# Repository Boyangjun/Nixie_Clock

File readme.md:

First of all, what is a nixie clock?

They are essentially timekeeping clocks, but nixie clock uses **nixie tube** to show the time. Nixie tube is a kind of ion tube that uses the principle of gas nixie discharge to work, the color of nixie determines by the composition of gas filled in the tube, such as neon to red,  argon to light purple, mercury to light blue, helium to pink and so on.

Nixie tube has some characteristics, such as power supply of 170V (so you need to do special boost), it’s life span is about one or two years, and keeping the number to tubes for a long time may lead to the cathode of tube poisoning(harmless for humans), so if you want to display the time, you need to do some small actions to change the numbers.

Light nixie is comfortable to look at, it will be a cool clock if together with RGB, Wi-Fi, temperature and humidity sensors, it should be a cool clock.

## Component Selection

* **Nixie Tube** I chose the IN-14 from the former Soviet Union, a new one costs 100 yuan, and a second-hand costs 50 yuan. In addition to the 0-9 numbers, there are left and right decimal points to show. It has a nice color and high quality.
* **Main control chip**I chose Arduino atmega 328p , because it can be developed directly on Arduino IDE, which is convenient for Mac computers, and there are extension libraries that can simplify programming(although it’s not a good thing for learning)
* **Time Receive** I chose esp8266 12F to obtain global standard time via ump connection of NTP Server
* **Boost**I just buy others boost module which can boost 5V to 170V, I recommend to design by yourself but I don’t have time.
* **RGB**I chose ws2812, which is a common one, it show fast and accurate and can be develop easily by Arduino IDE.
* PS: I didn’t use **Time Chip** like DS1302, Its really a failure, if the connection to NTP Server is not good, time shows in a bad way like jumping a few seconds, and if no Wi-Fi, it is unable to obtain time. To solve this problem, I added  DS3231 time count module, so it only need to get time when switching on, even if the power cut off, the time can be continued by button battery power.

## Circuit Design

* Nixie Clock Driver: 74HC595 + A42triode, easy to design and saving IO ports.

## Program Design

Program consist of two parts: setup() and loop(), the former only run once after power on, while loop() runs once and once until power off. So setup() contains some initialize likeWi-Fi connection, NTP Server connection, RGB, etc. While Loop() keeps receiving time  every second (or faster) and some other functions.

Some great libraries here, Thanks to their author!

Wifi and NTP Server：https://github.com/bportaluri/WiFiEsp

75HC595 Driver：[GitHub - Simsso/ShiftRegister74HC595: Arduino library that simplifies the usage of shift registers](https://github.com/Simsso/ShiftRegister74HC595)

RGB Driver：https://github.com/adafruit/Adafruit_NeoPixel

## Finally
I really hope this will help you for designing nixie clock. Any questions or suggestions, e-mail me! (boyangjun@bupt.edu.cn)

[image:BA12CFBF-97E2-4782-B7CB-3B10783BA695-6988-0000322A6EA5FA8B/IMG_20190530_185942.jpg]

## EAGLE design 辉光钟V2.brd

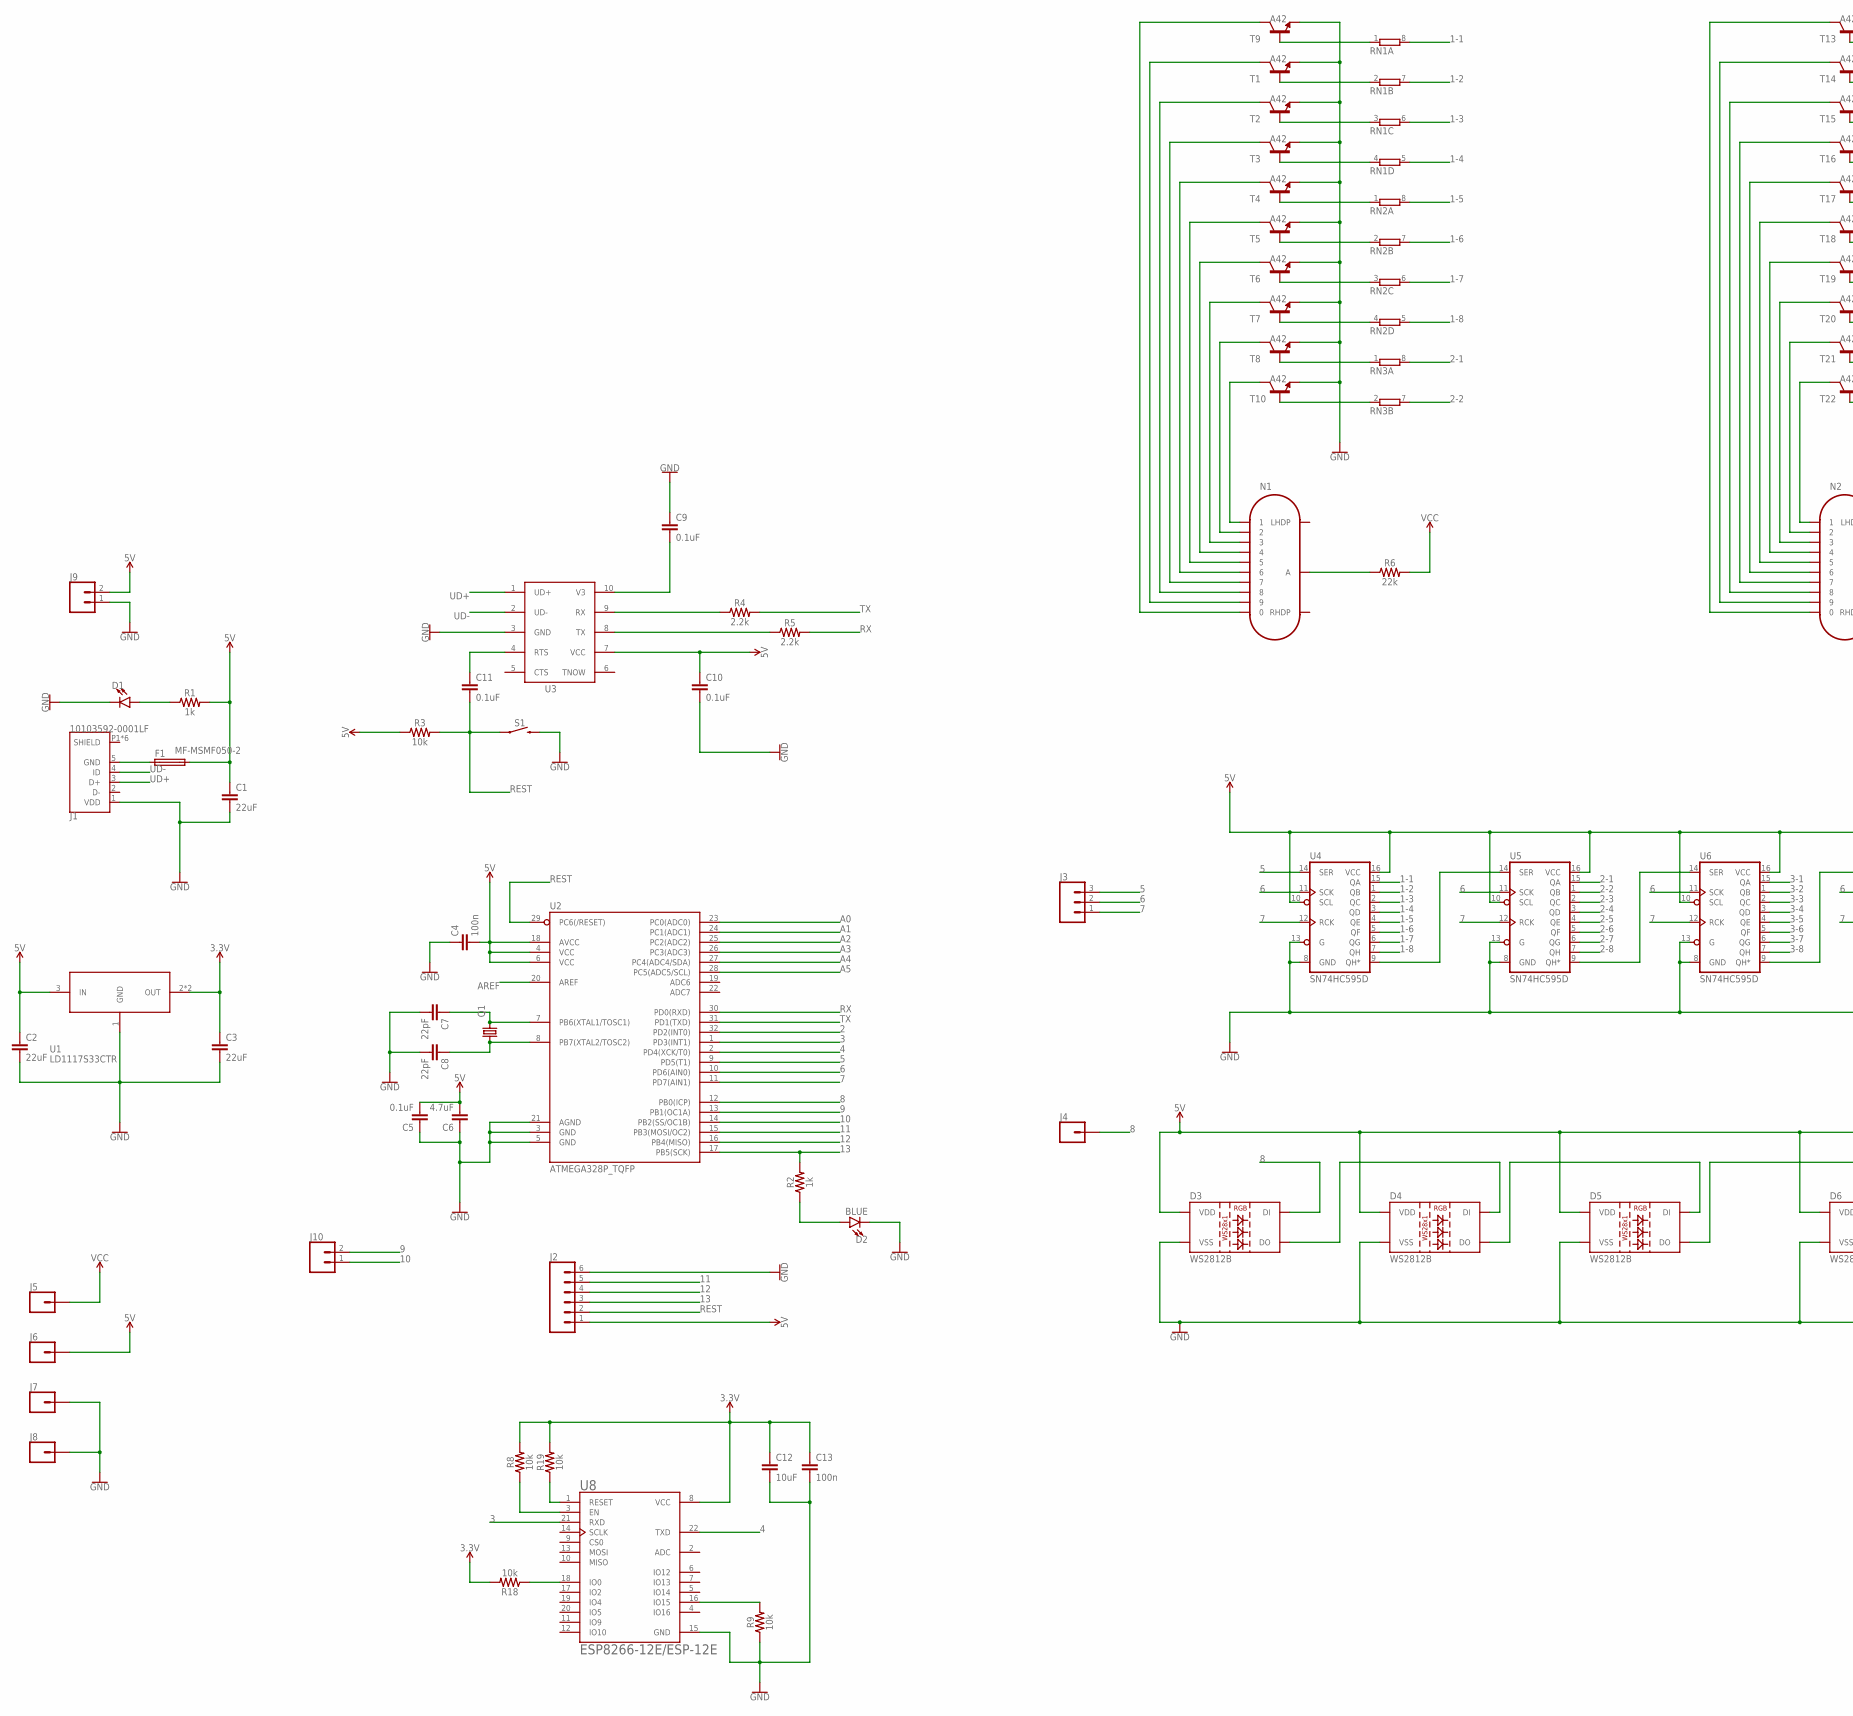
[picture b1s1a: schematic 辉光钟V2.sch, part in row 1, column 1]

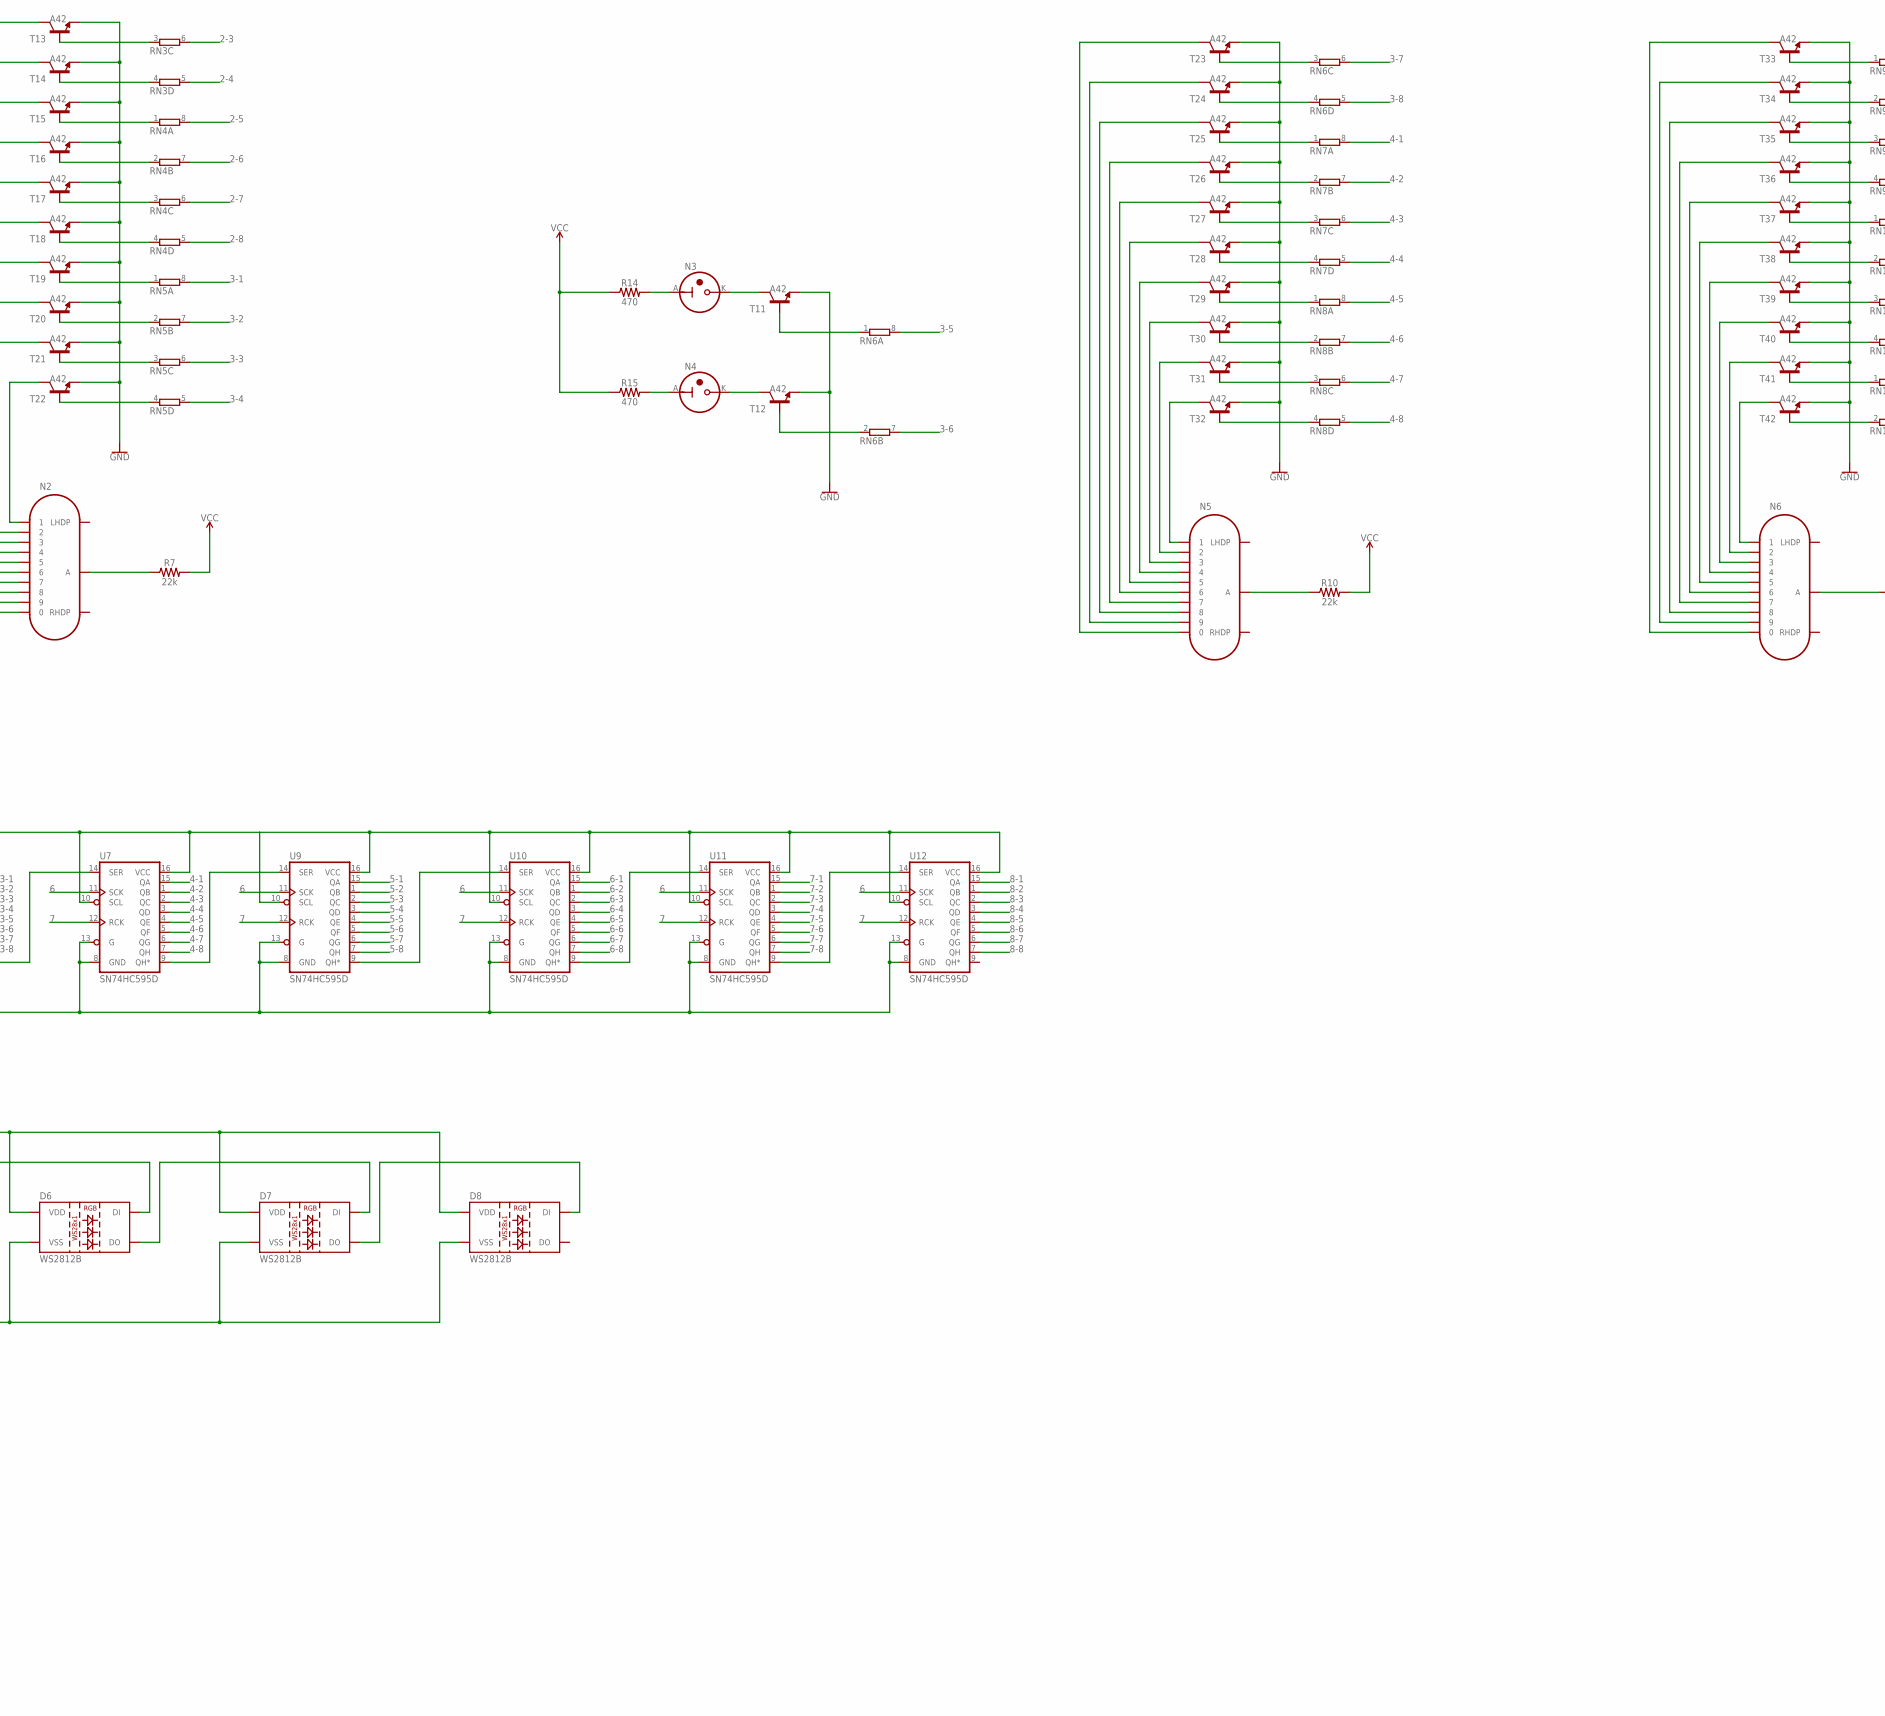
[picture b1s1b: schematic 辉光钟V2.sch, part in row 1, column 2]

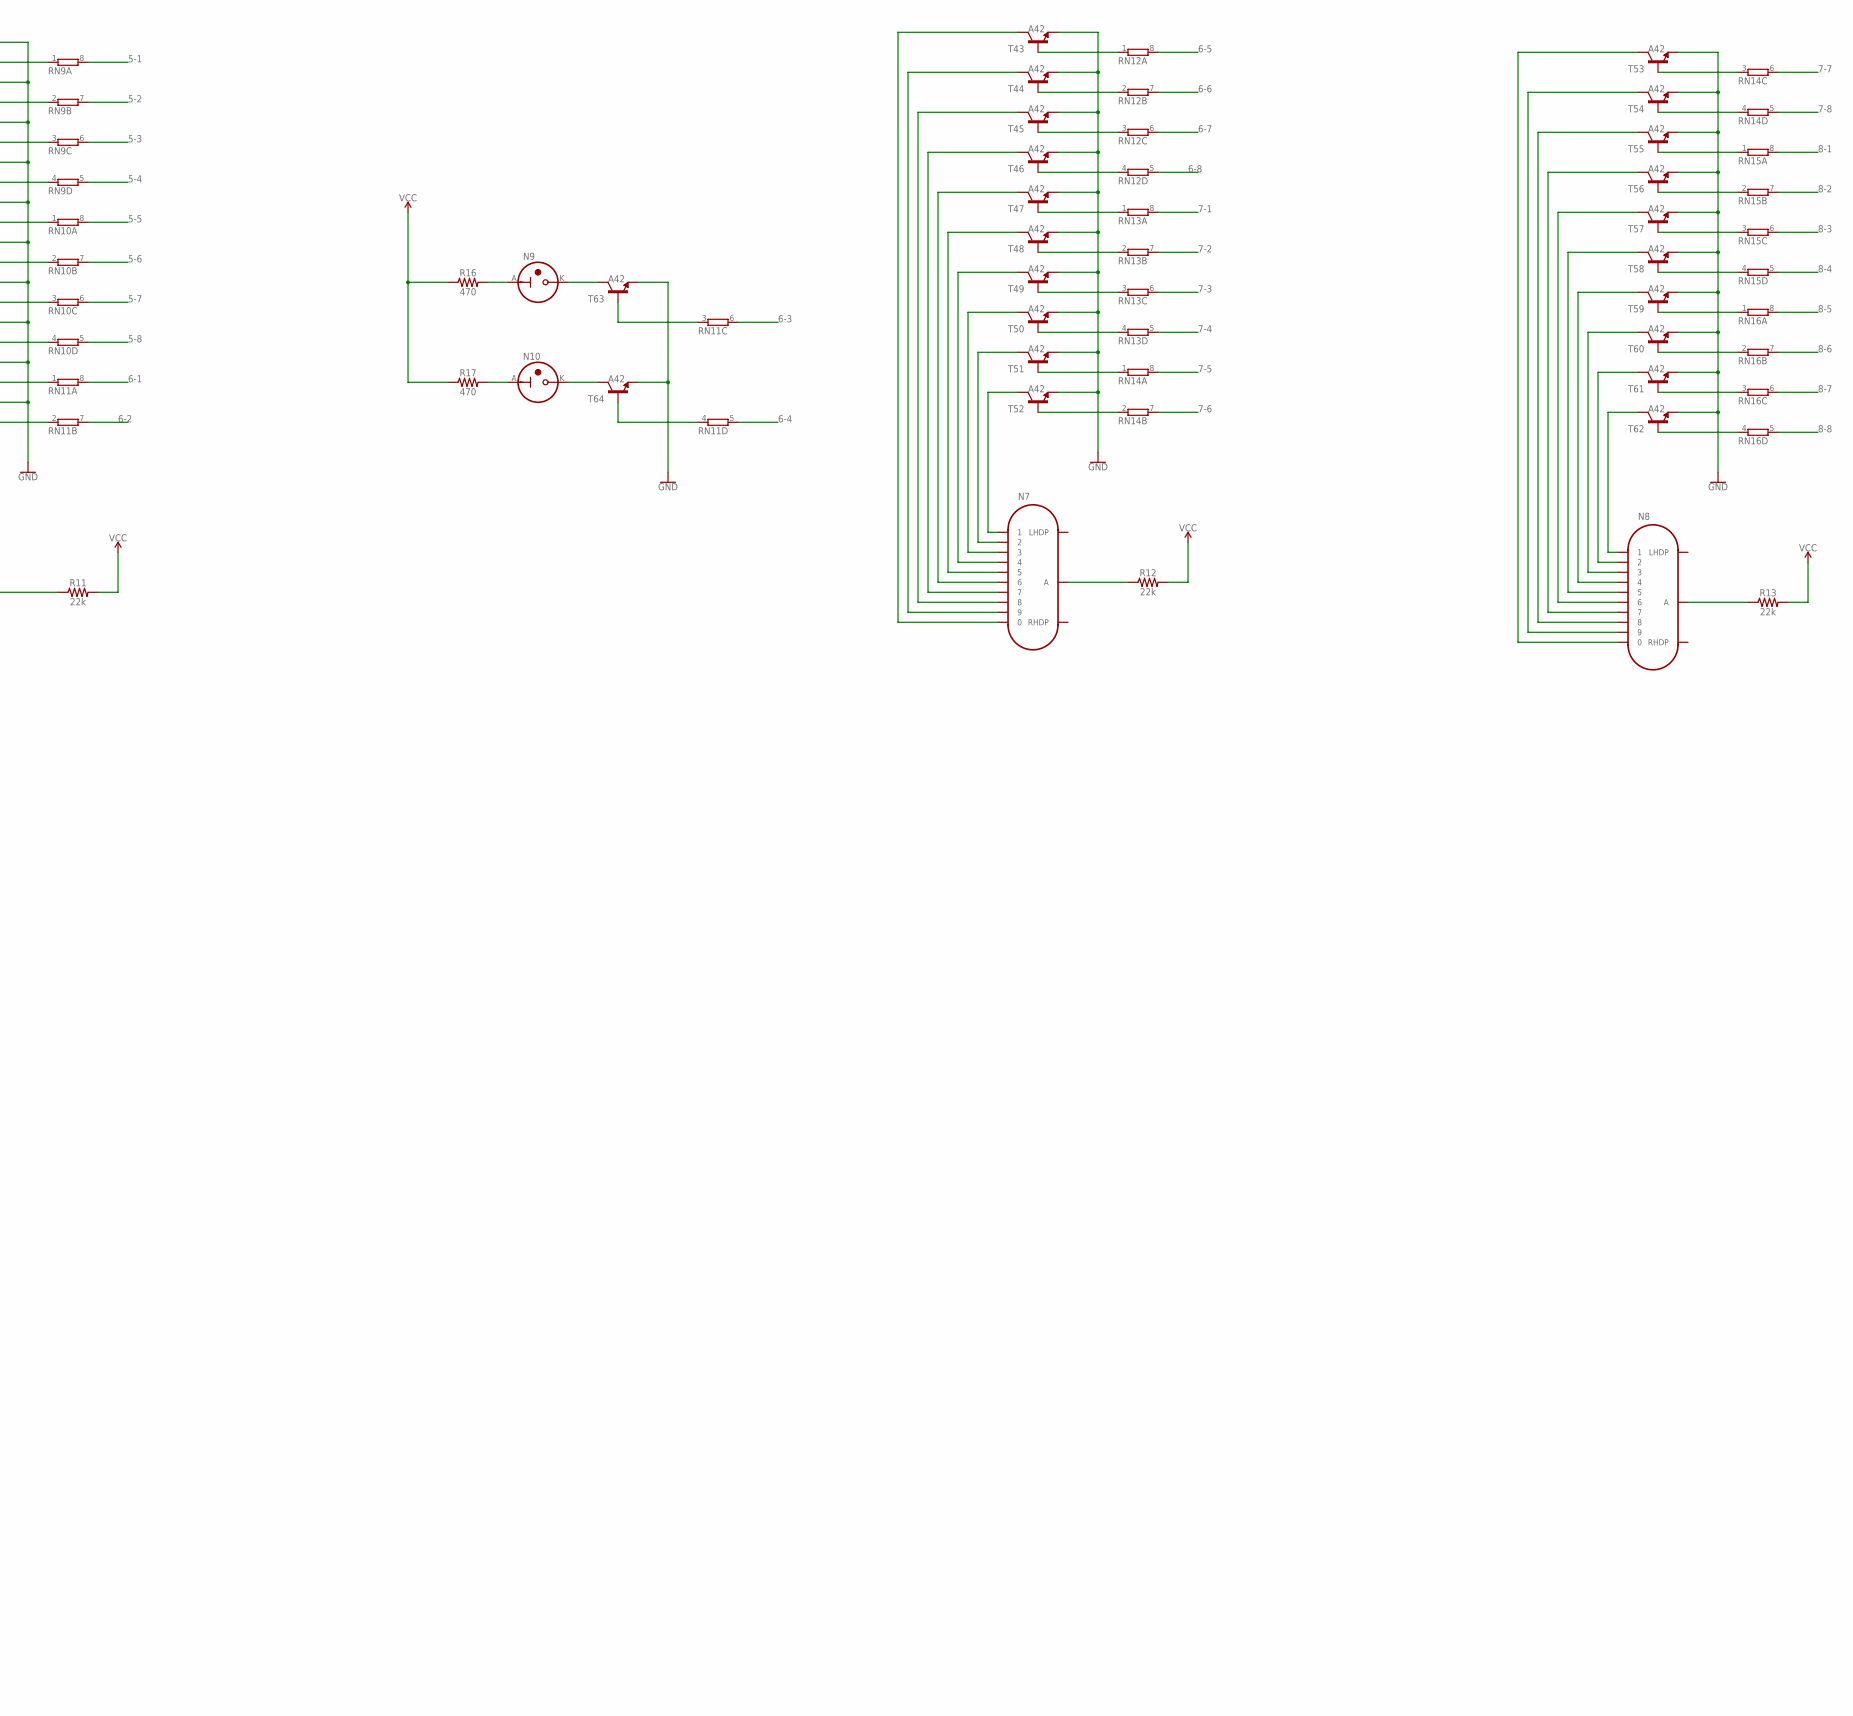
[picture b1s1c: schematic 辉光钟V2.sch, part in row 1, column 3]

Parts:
C1, C2, C3: 22uF; 0805
C4, C13: 100n; 0603
C5, C9, C10, C11: 0.1uF; 0603
C6: 4.7uF; 0603
C7, C8: 22pF; 0603
C12: 10uF; 0603
D1: LED0603; LED-0603
D2: BLUE; LED-0603
D3, D4, D5, D6, D7, D8: WS2812B
F1: MF-MSMF050-2; FUSM1812X02
J1: 10103592-0001LF; AMPHENOL_10103592-0001LF
J2: CONN_06NO_SILK_FEMALE_PTH; 1X06_NO_SILK
J3: CONN_03; 1X03
J4, J5, J6, J7, J8: CONN_01; 1X01
J9, J10: CONN_02; 1X02
N1, N2, N5, N6, N7, N8: IN-14
N3, N4, N9, N10: IN-3
Q1: KX-7; 3.2X2.5_KX-7
R1, R2: 1k; 0603
R3, R8, R9, R18, R19: 10k; 0603
R4, R5: 2.2k; 0603
R6, R7, R10, R11, R12, R13: 22k; 0603
R14, R15, R16, R17: 470; 0603
RN1, RN2, RN3, RN4, RN5, RN6, RN7, RN8, RN9, RN10, RN11, RN12, RN13, RN14, RN15, RN16: 4R-N0603-ARC; 0603-ARC
S1: MOMENTARY-SWITCH-SPST-SMD-6.0X3.5MM; TACTILE_SWITCH_SMD_6.0X3.5MM
T1, T2, T3, T4, T5, T6, T7, T8, T9, T10, T11, T12, T13, T14, T15, T16, T17, T18, T19, T20, T21, T22, T23, T24, T25, T26, T27, T28, T29, T30, T31, T32, T33, T34, T35, T36, T37, T38, T39, T40, T41, T42, T43, T44, T45, T46, T47, T48, T49, T50, T51, T52, T53, T54, T55, T56, T57, T58, T59, T60, T61, T62, T63, T64: A42; SOT23
U1: LD1117S33CTR; SOT223
U2: ATMEGA328P_TQFP; TQFP32-08
U3: CH340ESMD; MSOP10
U4, U5, U6, U7, U9, U10, U11, U12: SN74HC595D; SO16
U8: ESP8266-12E/ESP-12E; XCVR_ESP8266-12E/ESP-12E

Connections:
1-1: RN1.8 (2), U4.15 (QA)
1-2: RN1.7 (2), U4.1 (QB)
1-3: RN1.6 (2), U4.2 (QC)
1-4: RN1.5 (2), U4.3 (QD)
1-5: RN2.8 (2), U4.4 (QE)
1-6: RN2.7 (2), U4.5 (QF)
1-7: RN2.6 (2), U4.6 (QG)
1-8: RN2.5 (2), U4.7 (QH)
2: U2.32 (PD2(INT0))
2-1: RN3.8 (2), U5.15 (QA)
2-2: RN3.7 (2), U5.1 (QB)
2-3: RN3.6 (2), U5.2 (QC)
2-4: RN3.5 (2), U5.3 (QD)
2-5: RN4.8 (2), U5.4 (QE)
2-6: RN4.7 (2), U5.5 (QF)
2-7: RN4.6 (2), U5.6 (QG)
2-8: RN4.5 (2), U5.7 (QH)
3: U2.1 (PD3(INT1)), U8.21 (RXD)
3-1: RN5.8 (2), U6.15 (QA)
3-2: RN5.7 (2), U6.1 (QB)
3-3: RN5.6 (2), U6.2 (QC)
3-4: RN5.5 (2), U6.3 (QD)
3-5: RN6.8 (2), U6.4 (QE)
3-6: RN6.7 (2), U6.5 (QF)
3-7: RN6.6 (2), U6.6 (QG)
3-8: RN6.5 (2), U6.7 (QH)
3.3V: C3.1, C12.1, C13.1, R8.2, R18.2, R19.2, U1.2 (OUT), U1.4 (OUT), U8.8 (VCC)
4: U2.2 (PD4(XCK/T0)), U8.22 (TXD)
4-1: RN7.8 (2), U7.15 (QA)
4-2: RN7.7 (2), U7.1 (QB)
4-3: RN7.6 (2), U7.2 (QC)
4-4: RN7.5 (2), U7.3 (QD)
4-5: RN8.8 (2), U7.4 (QE)
4-6: RN8.7 (2), U7.5 (QF)
4-7: RN8.6 (2), U7.6 (QG)
4-8: RN8.5 (2), U7.7 (QH)
5: J3.3, U2.9 (PD5(T1)), U4.14 (SER)
5-1: RN9.8 (2), U9.15 (QA)
5-2: RN9.7 (2), U9.1 (QB)
5-3: RN9.6 (2), U9.2 (QC)
5-4: RN9.5 (2), U9.3 (QD)
5-5: RN10.8 (2), U9.4 (QE)
5-6: RN10.7 (2), U9.5 (QF)
5-7: RN10.6 (2), U9.6 (QG)
5-8: RN10.5 (2), U9.7 (QH)
5V: C1.1, C2.1, C4.2, C5.2, C6.2, C10.1, D3.1 (VDD), D4.1 (VDD), D5.1 (VDD), D6.1 (VDD), D7.1 (VDD), D8.1 (VDD), F1.2, J2.1, J6.1, J9.2, R1.2, R3.1, U1.3 (IN), U2.4 (VCC), U2.6 (VCC), U2.18 (AVCC), U3.7 (VCC), U4.10 (SCL), U4.16 (VCC), U5.10 (SCL), U5.16 (VCC), U6.10 (SCL), U6.16 (VCC), U7.10 (SCL), U7.16 (VCC), U9.10 (SCL), U9.16 (VCC), U10.10 (SCL), U10.16 (VCC), U11.10 (SCL), U11.16 (VCC), U12.10 (SCL), U12.16 (VCC)
6: J3.2, U2.10 (PD6(AIN0)), U4.11 (SCK), U5.11 (SCK), U6.11 (SCK), U7.11 (SCK), U9.11 (SCK), U10.11 (SCK), U11.11 (SCK), U12.11 (SCK)
6-1: RN11.8 (2), U10.15 (QA)
6-2: RN11.7 (2), U10.1 (QB)
6-3: RN11.6 (2), U10.2 (QC)
6-4: RN11.5 (2), U10.3 (QD)
6-5: RN12.8 (2), U10.4 (QE)
6-6: RN12.7 (2), U10.5 (QF)
6-7: RN12.6 (2), U10.6 (QG)
6-8: RN12.5 (2), U10.7 (QH)
7: J3.1, U2.11 (PD7(AIN1)), U4.12 (RCK), U5.12 (RCK), U6.12 (RCK), U7.12 (RCK), U9.12 (RCK), U10.12 (RCK), U11.12 (RCK), U12.12 (RCK)
7-1: RN13.8 (2), U11.15 (QA)
7-2: RN13.7 (2), U11.1 (QB)
7-3: RN13.6 (2), U11.2 (QC)
7-4: RN13.5 (2), U11.3 (QD)
7-5: RN14.8 (2), U11.4 (QE)
7-6: RN14.7 (2), U11.5 (QF)
7-7: RN14.6 (2), U11.6 (QG)
7-8: RN14.5 (2), U11.7 (QH)
8: D3.4 (DI), J4.1, U2.12 (PB0(ICP))
8-1: RN15.8 (2), U12.15 (QA)
8-2: RN15.7 (2), U12.1 (QB)
8-3: RN15.6 (2), U12.2 (QC)
8-4: RN15.5 (2), U12.3 (QD)
8-5: RN16.8 (2), U12.4 (QE)
8-6: RN16.7 (2), U12.5 (QF)
8-7: RN16.6 (2), U12.6 (QG)
8-8: RN16.5 (2), U12.7 (QH)
9: J10.2, U2.13 (PB1(OC1A))
10: J10.1, U2.14 (PB2(SS/OC1B))
11: J2.5, U2.15 (PB3(MOSI/OC2))
12: J2.4, U2.16 (PB4(MISO))
13: J2.3, R2.2, U2.17 (PB5(SCK))
A0: U2.23 (PC0(ADC0))
A1: U2.24 (PC1(ADC1))
A2: U2.25 (PC2(ADC2))
A3: U2.26 (PC3(ADC3))
A4: U2.27 (PC4(ADC4/SDA))
A5: U2.28 (PC5(ADC5/SCL))
AREF: U2.20 (AREF)
GND: C1.2, C2.2, C3.2, C4.1, C5.1, C6.1, C7.2, C8.2, C9.1, C10.2, C12.2, C13.2, D1.C, D2.C, D3.3 (VSS), D4.3 (VSS), D5.3 (VSS), D6.3 (VSS), D7.3 (VSS), D8.3 (VSS), J1.1 (VDD), J2.6, J7.1, J8.1, J9.1, R9.1, S1.2, T1.2 (E), T2.2 (E), T3.2 (E), T4.2 (E), T5.2 (E), T6.2 (E), T7.2 (E), T8.2 (E), T9.2 (E), T10.2 (E), T11.2 (E), T12.2 (E), T13.2 (E), T14.2 (E), T15.2 (E), T16.2 (E), T17.2 (E), T18.2 (E), T19.2 (E), T20.2 (E), T21.2 (E), T22.2 (E), T23.2 (E), T24.2 (E), T25.2 (E), T26.2 (E), T27.2 (E), T28.2 (E), T29.2 (E), T30.2 (E), T31.2 (E), T32.2 (E), T33.2 (E), T34.2 (E), T35.2 (E), T36.2 (E), T37.2 (E), T38.2 (E), T39.2 (E), T40.2 (E), T41.2 (E), T42.2 (E), T43.2 (E), T44.2 (E), T45.2 (E), T46.2 (E), T47.2 (E), T48.2 (E), T49.2 (E), T50.2 (E), T51.2 (E), T52.2 (E), T53.2 (E), T54.2 (E), T55.2 (E), T56.2 (E), T57.2 (E), T58.2 (E), T59.2 (E), T60.2 (E), T61.2 (E), T62.2 (E), T63.2 (E), T64.2 (E), U1.1 (GND), U2.3 (GND), U2.5 (GND), U2.21 (AGND), U3.3 (GND), U4.8 (GND), U4.13 (G), U5.8 (GND), U5.13 (G), U6.8 (GND), U6.13 (G), U7.8 (GND), U7.13 (G), U8.15 (GND), U9.8 (GND), U9.13 (G), U10.8 (GND), U10.13 (G), U11.8 (GND), U11.13 (G), U12.8 (GND), U12.13 (G)
unnamed: F1.1, J1.5 (GND)
unnamed: U4.9 (QH*), U5.14 (SER)
unnamed: U5.9 (QH*), U6.14 (SER)
unnamed: C7.1, Q1.3 (2), U2.7 (PB6(XTAL1/TOSC1))
unnamed: D1.A, R1.1
unnamed: C8.1, Q1.1, U2.8 (PB7(XTAL2/TOSC2))
unnamed: U6.9 (QH*), U7.14 (SER)
unnamed: D2.A, R2.1
unnamed: C11.1, U3.4 (RTS)
unnamed: N1.1, T10.3 (C)
unnamed: N1.2, T8.3 (C)
unnamed: N1.3, T7.3 (C)
unnamed: N1.4, T6.3 (C)
unnamed: N1.5, T5.3 (C)
unnamed: N1.6, T4.3 (C)
unnamed: N1.7, T3.3 (C)
unnamed: N1.8, T2.3 (C)
unnamed: N1.9, T1.3 (C)
unnamed: N1.0, T9.3 (C)
unnamed: RN1.1, T9.1 (B)
unnamed: RN1.2 (1), T1.1 (B)
unnamed: RN1.3 (1), T2.1 (B)
unnamed: RN1.4 (1), T3.1 (B)
unnamed: R4.1, U3.9 (RX)
unnamed: R5.1, U3.8 (TX)
unnamed: RN2.1, T4.1 (B)
unnamed: RN2.2 (1), T5.1 (B)
unnamed: C9.2, U3.10 (V3)
unnamed: RN2.3 (1), T6.1 (B)
unnamed: RN2.4 (1), T7.1 (B)
unnamed: N1.A, R6.1
unnamed: RN3.1, T8.1 (B)
unnamed: RN3.2 (1), T10.1 (B)
unnamed: N2.1, T22.3 (C)
unnamed: N2.2, T21.3 (C)
unnamed: N2.3, T20.3 (C)
unnamed: N2.4, T19.3 (C)
unnamed: N2.5, T18.3 (C)
unnamed: N2.6, T17.3 (C)
unnamed: N2.7, T16.3 (C)
unnamed: N2.8, T15.3 (C)
unnamed: N2.9, T14.3 (C)
unnamed: N2.0, T13.3 (C)
unnamed: N2.A, R7.1
unnamed: RN3.3 (1), T13.1 (B)
unnamed: RN3.4 (1), T14.1 (B)
unnamed: RN4.1, T15.1 (B)
unnamed: RN4.2 (1), T16.1 (B)
unnamed: RN4.3 (1), T17.1 (B)
unnamed: RN4.4 (1), T18.1 (B)
unnamed: RN5.1, T19.1 (B)
unnamed: RN5.2 (1), T20.1 (B)
unnamed: RN5.3 (1), T21.1 (B)
unnamed: RN5.4 (1), T22.1 (B)
unnamed: R8.1, U8.3 (EN)
unnamed: R9.2, U8.16 (IO15)
unnamed: U7.9 (QH*), U9.14 (SER)
unnamed: N5.1, T32.3 (C)
unnamed: N5.2, T31.3 (C)
unnamed: N5.3, T30.3 (C)
unnamed: N5.4, T29.3 (C)
unnamed: N5.5, T28.3 (C)
unnamed: N5.6, T27.3 (C)
unnamed: N5.7, T26.3 (C)
unnamed: N5.8, T25.3 (C)
unnamed: N5.9, T24.3 (C)
unnamed: N5.0, T23.3 (C)
unnamed: N5.A, R10.1
unnamed: RN6.3 (1), T23.1 (B)
unnamed: RN6.4 (1), T24.1 (B)
unnamed: RN7.1, T25.1 (B)
unnamed: RN7.2 (1), T26.1 (B)
unnamed: RN7.3 (1), T27.1 (B)
unnamed: RN7.4 (1), T28.1 (B)
unnamed: RN8.1, T29.1 (B)
unnamed: RN8.2 (1), T30.1 (B)
unnamed: RN8.3 (1), T31.1 (B)
unnamed: RN8.4 (1), T32.1 (B)
unnamed: N6.1, T42.3 (C)
unnamed: N6.2, T41.3 (C)
unnamed: N6.3, T40.3 (C)
unnamed: N6.4, T39.3 (C)
unnamed: N6.5, T38.3 (C)
unnamed: N6.6, T37.3 (C)
unnamed: N6.7, T36.3 (C)
unnamed: N6.8, T35.3 (C)
unnamed: N6.9, T34.3 (C)
unnamed: N6.0, T33.3 (C)
unnamed: N6.A, R11.1
unnamed: RN9.1, T33.1 (B)
unnamed: RN9.2 (1), T34.1 (B)
unnamed: RN9.3 (1), T35.1 (B)
unnamed: RN9.4 (1), T36.1 (B)
unnamed: RN10.1, T37.1 (B)
unnamed: RN10.2 (1), T38.1 (B)
unnamed: RN10.3 (1), T39.1 (B)
unnamed: RN10.4 (1), T40.1 (B)
unnamed: RN11.1, T41.1 (B)
unnamed: RN11.2 (1), T42.1 (B)
unnamed: N7.1, T52.3 (C)
unnamed: N7.2, T51.3 (C)
unnamed: N7.3, T50.3 (C)
unnamed: N7.4, T49.3 (C)
unnamed: N7.5, T48.3 (C)
unnamed: N7.6, T47.3 (C)
unnamed: N7.7, T46.3 (C)
unnamed: N7.8, T45.3 (C)
unnamed: N7.9, T44.3 (C)
unnamed: N7.0, T43.3 (C)
unnamed: N7.A, R12.1
unnamed: RN12.1, T43.1 (B)
unnamed: RN12.2 (1), T44.1 (B)
unnamed: RN12.3 (1), T45.1 (B)
unnamed: RN12.4 (1), T46.1 (B)
unnamed: RN13.1, T47.1 (B)
unnamed: RN13.2 (1), T48.1 (B)
unnamed: RN13.3 (1), T49.1 (B)
unnamed: RN13.4 (1), T50.1 (B)
unnamed: RN14.1, T51.1 (B)
unnamed: RN14.2 (1), T52.1 (B)
unnamed: N8.1, T62.3 (C)
unnamed: N8.2, T61.3 (C)
unnamed: N8.3, T60.3 (C)
unnamed: N8.4, T59.3 (C)
unnamed: N8.5, T58.3 (C)
unnamed: N8.6, T57.3 (C)
unnamed: N8.7, T56.3 (C)
unnamed: N8.8, T55.3 (C)
unnamed: N8.9, T54.3 (C)
unnamed: N8.0, T53.3 (C)
unnamed: N8.A, R13.1
unnamed: RN14.3 (1), T53.1 (B)
unnamed: RN14.4 (1), T54.1 (B)
unnamed: RN15.1, T55.1 (B)
unnamed: RN15.2 (1), T56.1 (B)
unnamed: RN15.3 (1), T57.1 (B)
unnamed: RN15.4 (1), T58.1 (B)
unnamed: RN16.1, T59.1 (B)
unnamed: RN16.2 (1), T60.1 (B)
unnamed: RN16.3 (1), T61.1 (B)
unnamed: RN16.4 (1), T62.1 (B)
unnamed: N3.A, R14.2
unnamed: N3.K, T11.3 (C)
unnamed: N4.A, R15.2
unnamed: N4.K, T12.3 (C)
unnamed: RN6.1, T11.1 (B)
unnamed: RN6.2 (1), T12.1 (B)
unnamed: N9.A, R16.2
unnamed: N9.K, T63.3 (C)
unnamed: N10.A, R17.2
unnamed: N10.K, T64.3 (C)
unnamed: RN11.3 (1), T63.1 (B)
unnamed: RN11.4 (1), T64.1 (B)
unnamed: R19.1, U8.1 (RESET)
unnamed: D3.2 (DO), D4.4 (DI)
unnamed: R18.1, U8.18 (IO0)
unnamed: D4.2 (DO), D5.4 (DI)
unnamed: D5.2 (DO), D6.4 (DI)
unnamed: D6.2 (DO), D7.4 (DI)
unnamed: D7.2 (DO), D8.4 (DI)
unnamed: U10.9 (QH*), U11.14 (SER)
unnamed: U11.9 (QH*), U12.14 (SER)
unnamed: U9.9 (QH*), U10.14 (SER)
REST: C11.2, J2.2, R3.2, S1.1, U2.29 (PC6(/RESET))
RX: R5.2, U2.30 (PD0(RXD))
SHIELD: J1.P1 (SHIELD), J1.P2 (SHIELD), J1.P3 (SHIELD), J1.P4 (SHIELD), J1.P5 (SHIELD), J1.P6 (SHIELD)
TX: R4.2, U2.31 (PD1(TXD))
UD+: J1.3 (D+), U3.1 (UD+)
UD-: J1.4 (ID), U3.2 (UD-)
VCC: J5.1, R6.2, R7.2, R10.2, R11.2, R12.2, R13.2, R14.1, R15.1, R16.1, R17.1

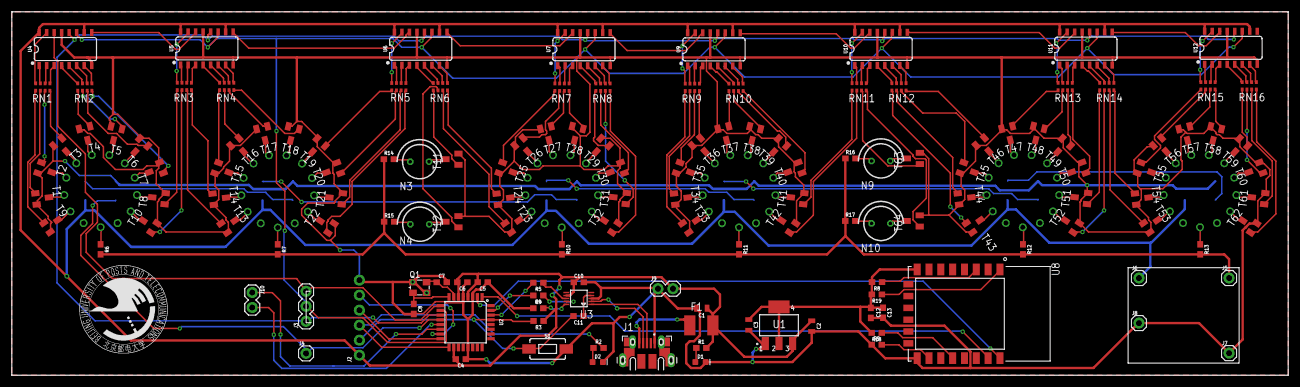
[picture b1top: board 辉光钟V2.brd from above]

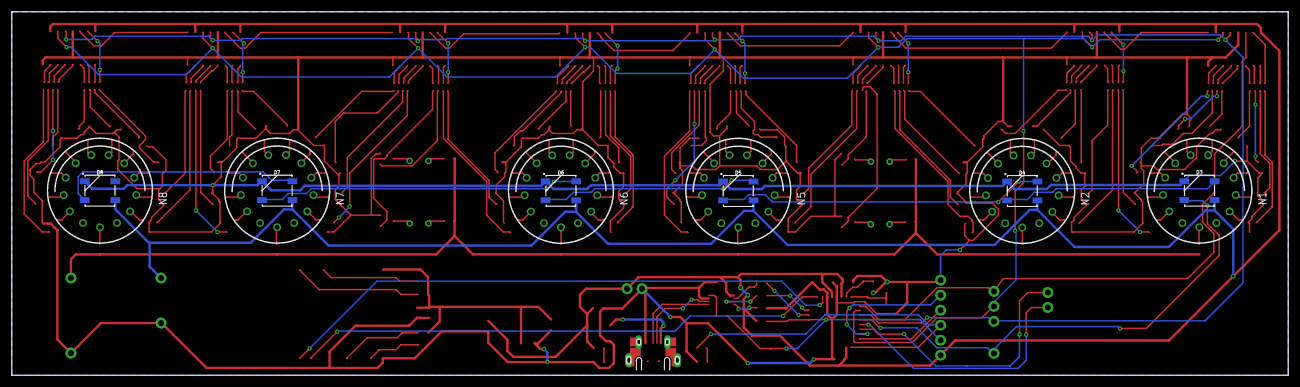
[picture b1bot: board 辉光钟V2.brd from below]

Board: 2 copper layers, 215.9 x 61.5 mm, 155 parts (12 on the bottom side), 248 nets.

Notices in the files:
parts and their libraries:
SparkFun-LED: Licensing: Creative Commons ShareAlike 4.0 International - https://creativecommons.org/licenses/by-sa/4.0
crystal-geyer_V1_0: Copyright: Geyer-Electronic
